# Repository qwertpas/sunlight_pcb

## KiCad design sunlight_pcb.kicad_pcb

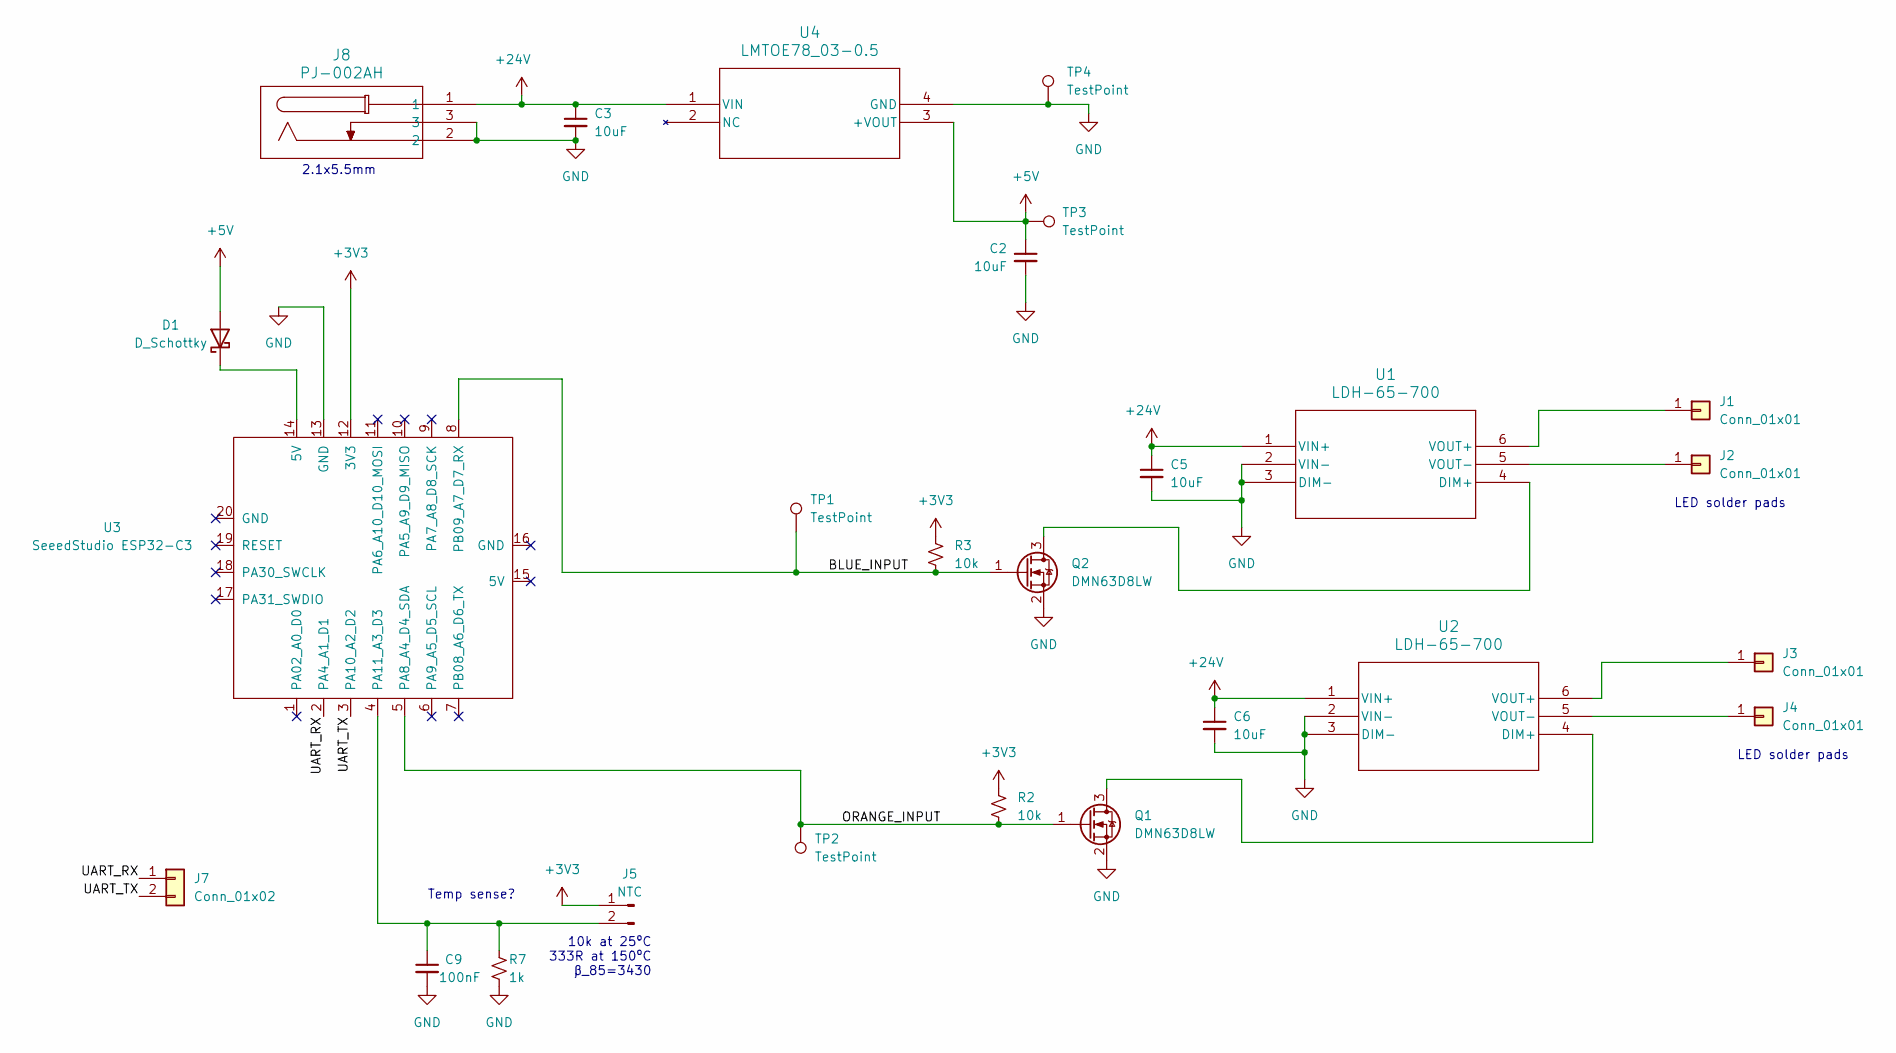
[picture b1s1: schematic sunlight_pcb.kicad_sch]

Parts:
C2, C3, C5, C6: 10uF; CP_Elec_5x5.3; MPN EMK1VM100D80D00R
C9: 100nF; C_0603_1608Metric_Pad1.08x0.95mm_HandSolder; MPN CL05A104KA5NNNC
D1: D_Schottky; D_0603_1608Metric_Pad1.05x0.95mm_HandSolder
J1, J2, J3, J4: Conn_01x01; SolderWire-2sqmm_1x01_D2mm_OD3.9mm
J5: NTC; SolderNTC-1.27mm
J7: Conn_01x02; PinHeader_1x02_P2.54mm_Vertical
J8: PJ-002AH; CUI_PJ-002AH
Q1, Q2: DMN63D8LW; SOT-323_SC-70_Handsoldering
R2, R3: 10k; D_0603_1608Metric_Pad1.05x0.95mm_HandSolder
R7: 1k; R_0603_1608Metric_Pad0.98x0.95mm_HandSolder; MPN RC0402FR-071KL
TP1, TP2, TP3, TP4: TestPoint; TestPoint_Pad_1.0x1.0mm
U1, U2: LDH-65-700; DIP6_LDH-65_MWU
U3: SeeedStudio ESP32-C3; XIAO-ESP32C3-14P-2.54-21X17.8MM
U4: LMTOE78_03-0.5; LMTOE78_0.5_GAP

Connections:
+3V3: J5.1, R2.1, R3.1, U3.12 (3V3)
+5V: C2.1, D1.2 (A), TP3.1, U4.3 (+VOUT)
+24V: C3.1, C5.1, C6.1, J8.1, U1.1 (VIN+), U2.1 (VIN+), U4.1 (VIN)
/BLUE_INPUT: Q2.1 (G), R3.2, TP1.1, U3.8 (PB09_A7_D7_RX)
/ORANGE_INPUT: Q1.1 (G), R2.2, TP2.1, U3.5 (PA8_A4_D4_SDA)
/UART_RX: J7.1, U3.2 (PA4_A1_D1)
/UART_TX: J7.2, U3.3 (PA10_A2_D2)
GND: C2.2, C3.2, C5.2, C6.2, J8.2, J8.3, Q1.2 (S), Q2.2 (S), TP4.1, U1.2 (VIN-), U1.3 (DIM-), U2.2 (VIN-), U2.3 (DIM-), U3.13 (GND), U4.4 (GND); also elsewhere on the board
unnamed: D1.1 (K), U3.14 (5V)
unnamed: J1.1, U1.6 (VOUT+)
unnamed: J2.1, U1.5 (VOUT-)
unnamed: J3.1, U2.6 (VOUT+)
unnamed: J4.1, U2.5 (VOUT-)
unnamed 13: J5.2, U3.4 (PA11_A3_D3); also elsewhere on the board
unnamed: Q1.3 (D), U2.4 (DIM+)
unnamed: Q2.3 (D), U1.4 (DIM+)

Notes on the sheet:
LED solder pads
2.1x5.5mm
Temp sense?
10k at 25ºC 333R at 150ºC β_85=3430

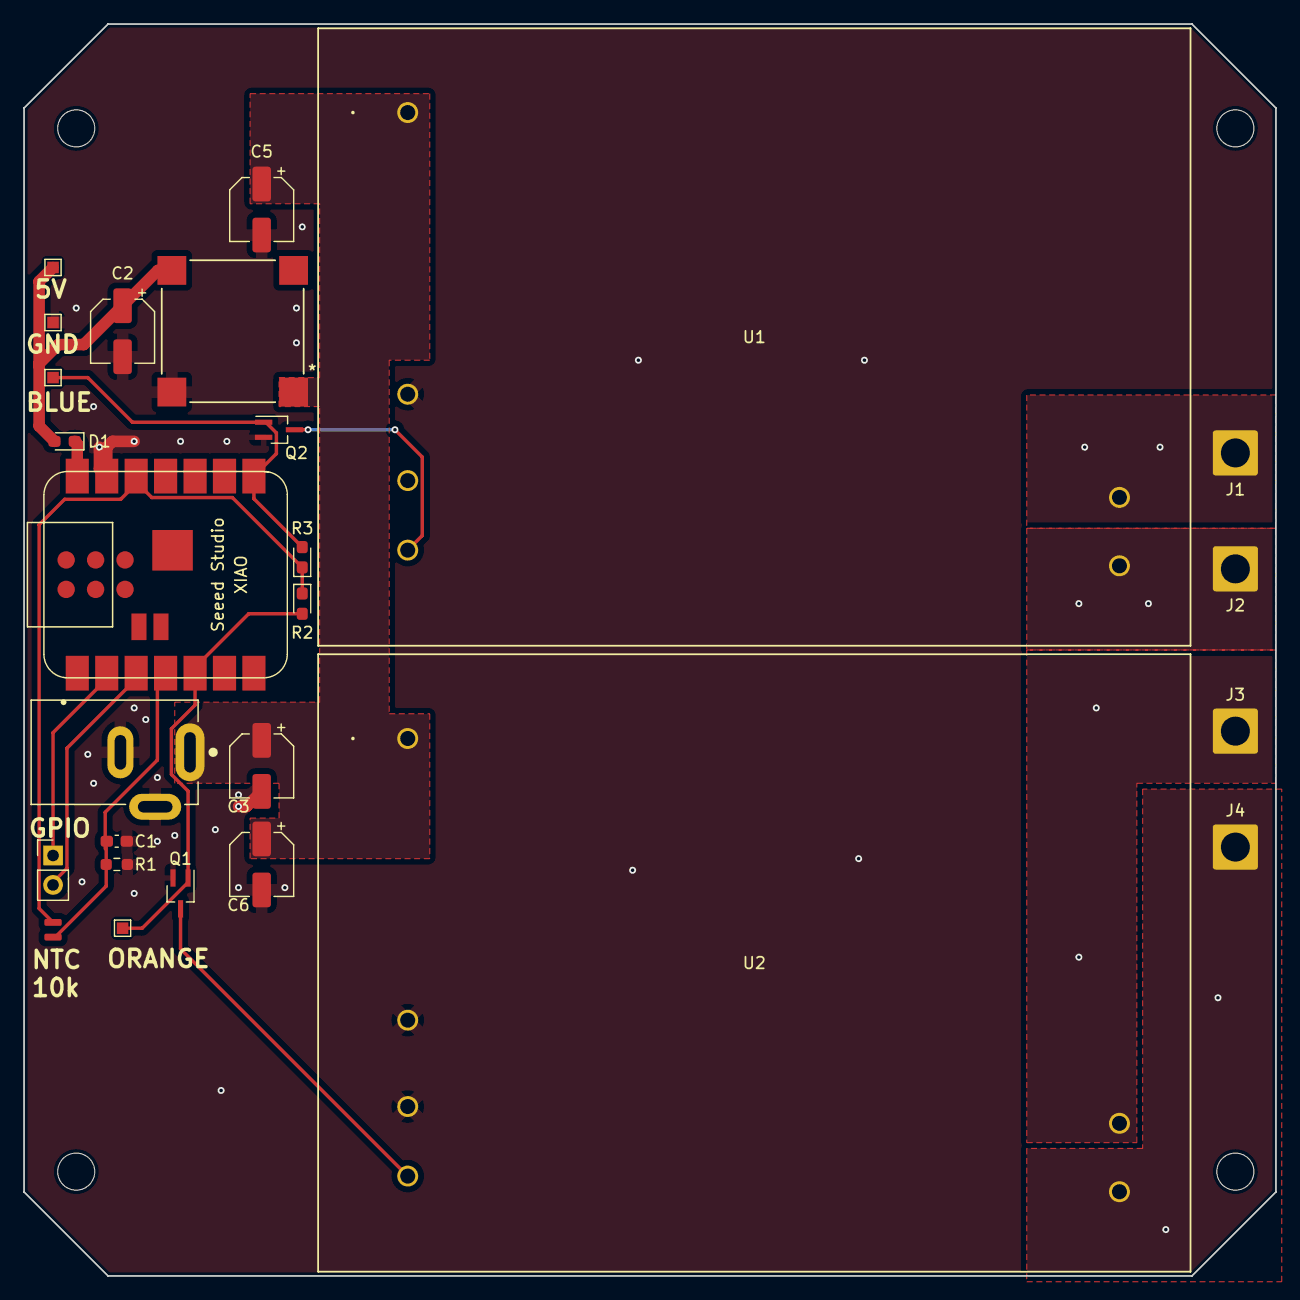
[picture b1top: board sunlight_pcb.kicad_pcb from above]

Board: 2 copper layers, 108.0 x 108.0 mm, 26 parts (0 on the bottom side), 16 nets.

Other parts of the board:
C1: 100nF; C_0603_1608Metric_Pad1.08x0.95mm_HandSolder
R1: 1k; R_0603_1608Metric_Pad0.98x0.95mm_HandSolder

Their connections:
GND: C1.2, R1.1; also elsewhere on the board
unnamed 13: C1.1, R1.2; also elsewhere on the board

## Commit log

2023-12-30 first commit schematic
2023-12-30 change barrel to tht and update 3d models
2024-01-04 layout done, gerbers gened
